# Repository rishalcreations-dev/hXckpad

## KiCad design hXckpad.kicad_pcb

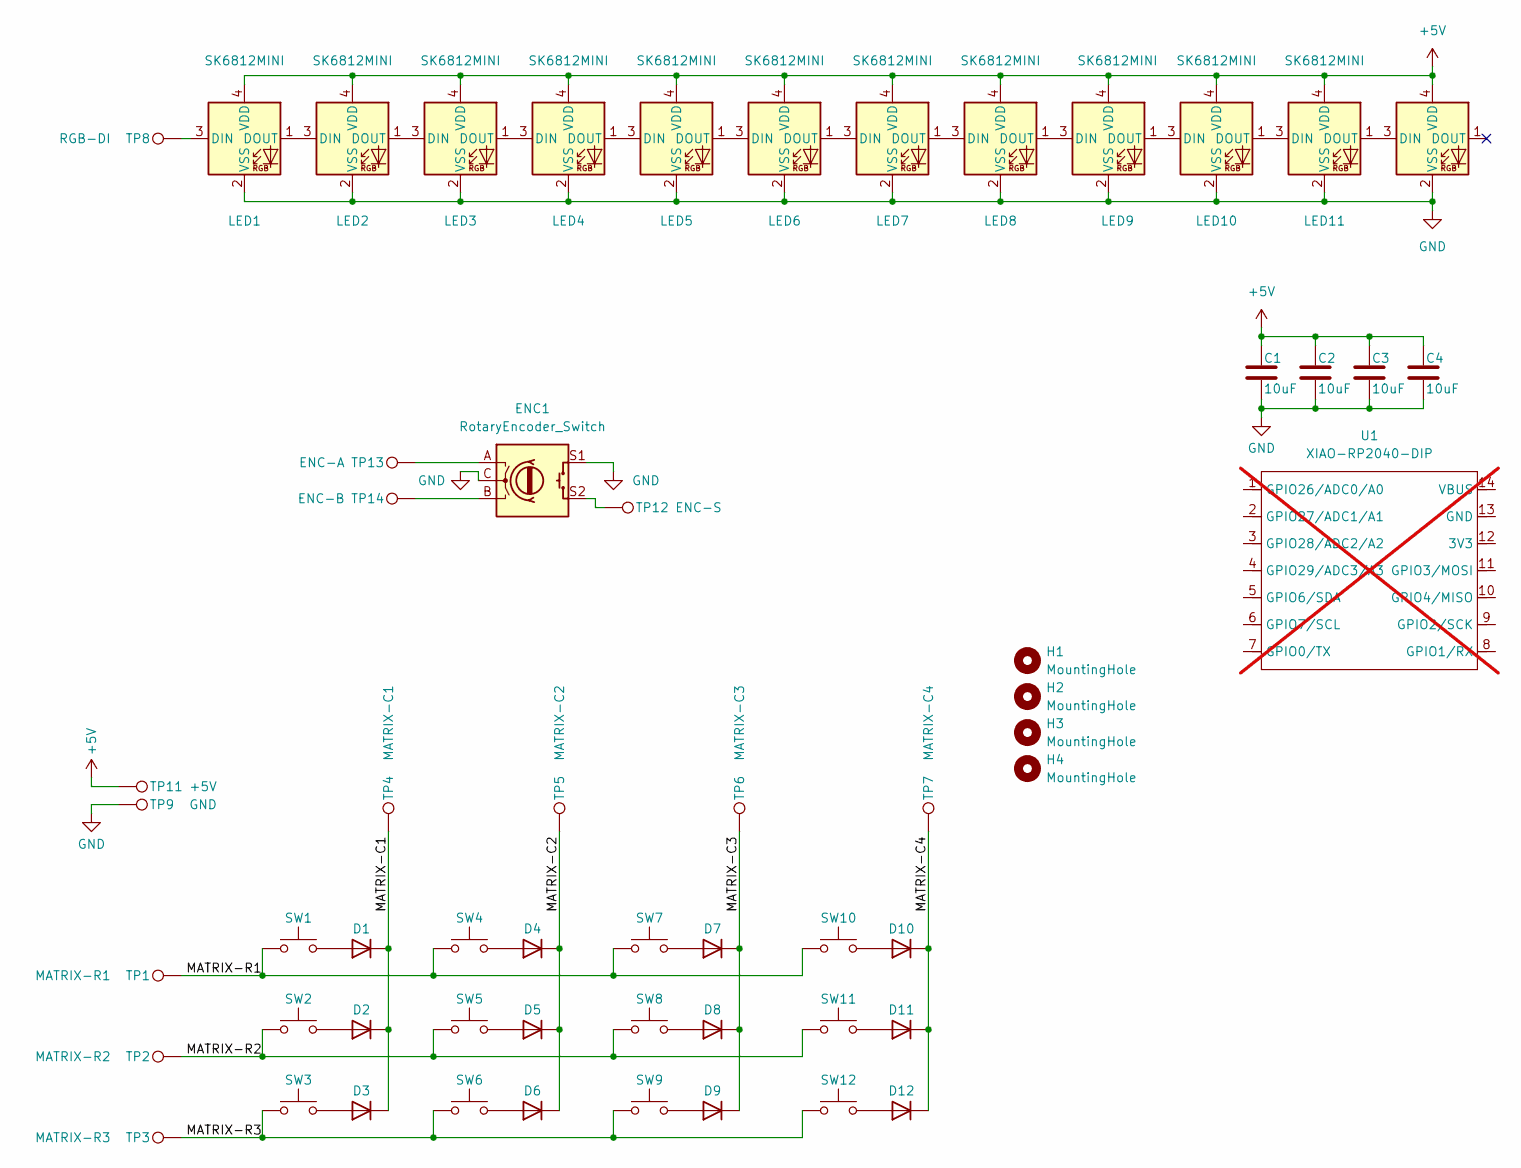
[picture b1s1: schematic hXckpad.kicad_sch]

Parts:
C1, C2, C3, C4: 10uF; C_0805_2012Metric
D1, D2, D3, D4, D5, D6, D7, D8, D9, D10, D11, D12: 1N4148; D_SOD-123F
ENC1: RotaryEncoder_Switch; RotaryEncoder_Alps_EC11E-Switch_Vertical_H20mm
H1, H2, H3, H4: MountingHole; MountingHole_2.2mm_M2
LED1, LED2, LED3, LED4, LED5, LED6, LED7, LED8, LED9, LED10, LED11, LED12: SK6812MINI; SK6812MINI-E
SW1, SW2, SW3, SW4, SW5, SW6, SW7, SW8, SW9, SW10, SW11, SW12: SW_Push; Gateron_LP_3.0_Hotswap
TP1: MATRIX-R1; TestPoint_Pad_D2.0mm
TP2: MATRIX-R2; TestPoint_Pad_D2.0mm
TP3: MATRIX-R3; TestPoint_Pad_D2.0mm
TP4: MATRIX-C1; TestPoint_Pad_D2.0mm
TP5: MATRIX-C2; TestPoint_Pad_D2.0mm
TP6: MATRIX-C3; TestPoint_Pad_D2.0mm
TP7: MATRIX-C4; TestPoint_Pad_D2.0mm
TP8: RGB-DI; TestPoint_Pad_D2.0mm
TP9: GND; TestPoint_Pad_D2.0mm
TP11: +5V; TestPoint_Pad_D2.0mm
TP12: ENC-S; TestPoint_Pad_D2.0mm
TP13: ENC-A; TestPoint_Pad_D2.0mm
TP14: ENC-B; TestPoint_Pad_D2.0mm
U1: XIAO-RP2040-DIP; PinHeader_2x07_P2.54mm_Vertical_SMD; not fitted

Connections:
+5V: C1.1, C2.1, C3.1, C4.1, LED1.4 (VDD), LED2.4 (VDD), LED3.4 (VDD), LED4.4 (VDD), LED5.4 (VDD), LED6.4 (VDD), LED7.4 (VDD), LED8.4 (VDD), LED9.4 (VDD), LED10.4 (VDD), LED11.4 (VDD), LED12.4 (VDD), TP11.1 (1_1)
/MATRIX-C1: D1.1 (K), D2.1 (K), D3.1 (K), TP4.1 (1_1)
/MATRIX-C2: D4.1 (K), D5.1 (K), D6.1 (K), TP5.1 (1_1)
/MATRIX-C3: D7.1 (K), D8.1 (K), D9.1 (K), TP6.1 (1_1)
/MATRIX-C4: D10.1 (K), D11.1 (K), D12.1 (K), TP7.1 (1_1)
/MATRIX-R1: SW1.1, SW4.1, SW7.1, SW10.1, TP1.1 (1_1)
/MATRIX-R2: SW2.1, SW5.1, SW8.1, SW11.1, TP2.1 (1_1)
/MATRIX-R3: SW3.1, SW6.1, SW9.1, SW12.1, TP3.1 (1_1)
GND: C1.2, C2.2, C3.2, C4.2, ENC1.C, ENC1.S1, LED1.2 (VSS), LED2.2 (VSS), LED3.2 (VSS), LED4.2 (VSS), LED5.2 (VSS), LED6.2 (VSS), LED7.2 (VSS), LED8.2 (VSS), LED9.2 (VSS), LED10.2 (VSS), LED11.2 (VSS), LED12.2 (VSS), TP9.1 (1_1)
unnamed: D1.2 (A), SW1.2
unnamed: D2.2 (A), SW2.2
unnamed: D3.2 (A), SW3.2
unnamed: D4.2 (A), SW4.2
unnamed: D5.2 (A), SW5.2
unnamed: D6.2 (A), SW6.2
unnamed: D7.2 (A), SW7.2
unnamed: D8.2 (A), SW8.2
unnamed: D9.2 (A), SW9.2
unnamed: D10.2 (A), SW10.2
unnamed: D11.2 (A), SW11.2
unnamed: D12.2 (A), SW12.2
unnamed: ENC1.A, TP13.1 (1_1)
unnamed: ENC1.B, TP14.1 (1_1)
unnamed: ENC1.S2, TP12.1 (1_1)
unnamed: LED1.3 (DIN), TP8.1 (1_1)
unnamed: LED1.1 (DOUT), LED2.3 (DIN)
unnamed: LED2.1 (DOUT), LED3.3 (DIN)
unnamed: LED3.1 (DOUT), LED4.3 (DIN)
unnamed: LED4.1 (DOUT), LED5.3 (DIN)
unnamed: LED5.1 (DOUT), LED6.3 (DIN)
unnamed: LED6.1 (DOUT), LED7.3 (DIN)
unnamed: LED7.1 (DOUT), LED8.3 (DIN)
unnamed: LED8.1 (DOUT), LED9.3 (DIN)
unnamed: LED9.1 (DOUT), LED10.3 (DIN)
unnamed: LED10.1 (DOUT), LED11.3 (DIN)
unnamed: LED11.1 (DOUT), LED12.3 (DIN)

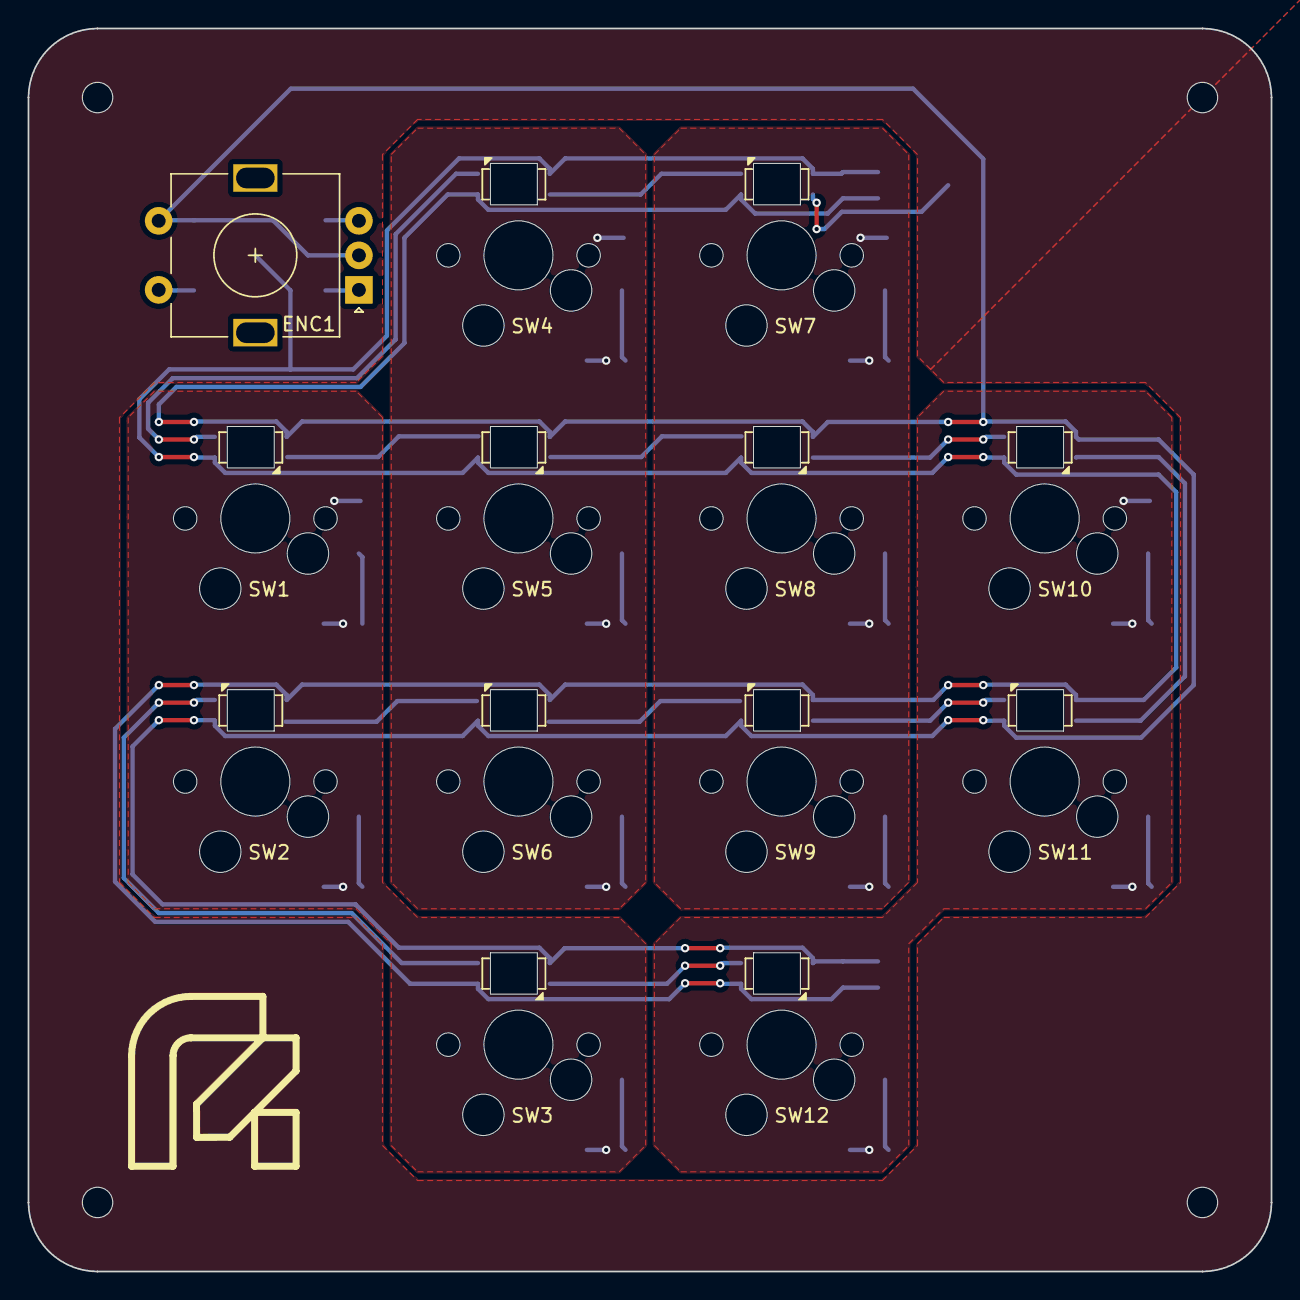
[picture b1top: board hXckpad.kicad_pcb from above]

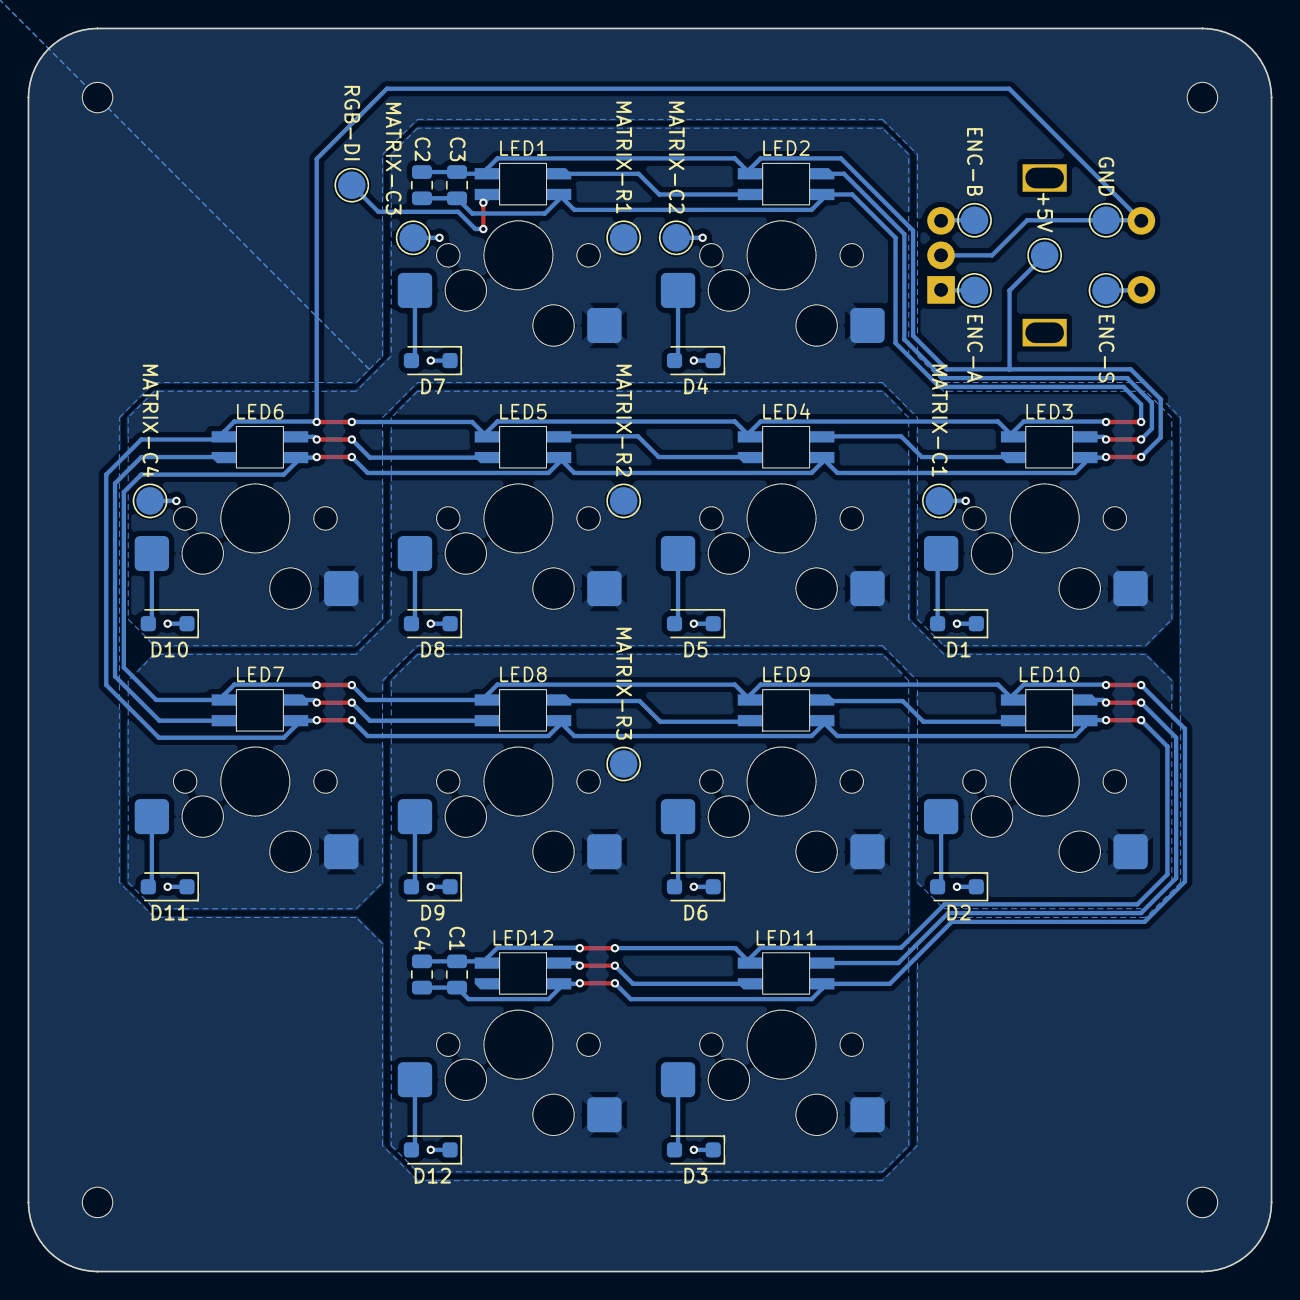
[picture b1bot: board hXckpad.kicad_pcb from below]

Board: 2 copper layers, 90.0 x 90.0 mm, 58 parts (41 on the bottom side), 36 nets.

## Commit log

2026-02-14 added sk assets
2026-02-14 Added 3D Files
2026-02-14 made it 3d
    i made it 3d
2026-02-14 Fixed the erc rules
    got rid of random line
    added an x to the end of the LED chain
    relabeled the numbers
2026-02-21 updates schematic annotations, and fixed the wiring convention, made the pcb, not routed, aligned to grid, in place
    updates schematic annotations, and fixed the wiring convention (gnd facing down, no right angle directly on pins, etc), made the pcb, not routed, aligned to grid, in right place
2026-02-21 placed edgu cut dxf from fusion
    exactly what is sounds like
2026-02-21 little fixes, added 3d models
2026-02-21 uncooked step
2026-02-21 started routing
2026-02-22 routed everything
    all things routed, partial drc ran
2026-02-22 moved 1 trace, added r logo silkscreen
    exactly what it sounds like
2026-05-05 micocontroller moved
    microcontroll moved 2 clicks up but still has bad routing
2026-05-30 stuff
2026-05-30 completed new routing
2026-05-30 Completed Routing
